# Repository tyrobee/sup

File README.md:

# Sup
A vtol that's highly customisible and reliable

i have been into the hobby of flying from planes to drone and really wanted to try and know abt the vtols from a long time and checking out there i didnt really find alot of good customisible options for vtol and in this process ive seen the zipline the company that aims to deliver stuff through drone have made their vtol for urban mobility which really inspired me and now im trying to build on my own which has the vtol capabilites for now as v1 and lets see if this goes thru well i may build that payload model as v2 ;)

The project works on a teensy 4.1 with a gyro9250 as the imu and the dRehmFlight firmware(https://github.com/nickrehm/dRehmFlight.git).

## PCB

### Front

### Back

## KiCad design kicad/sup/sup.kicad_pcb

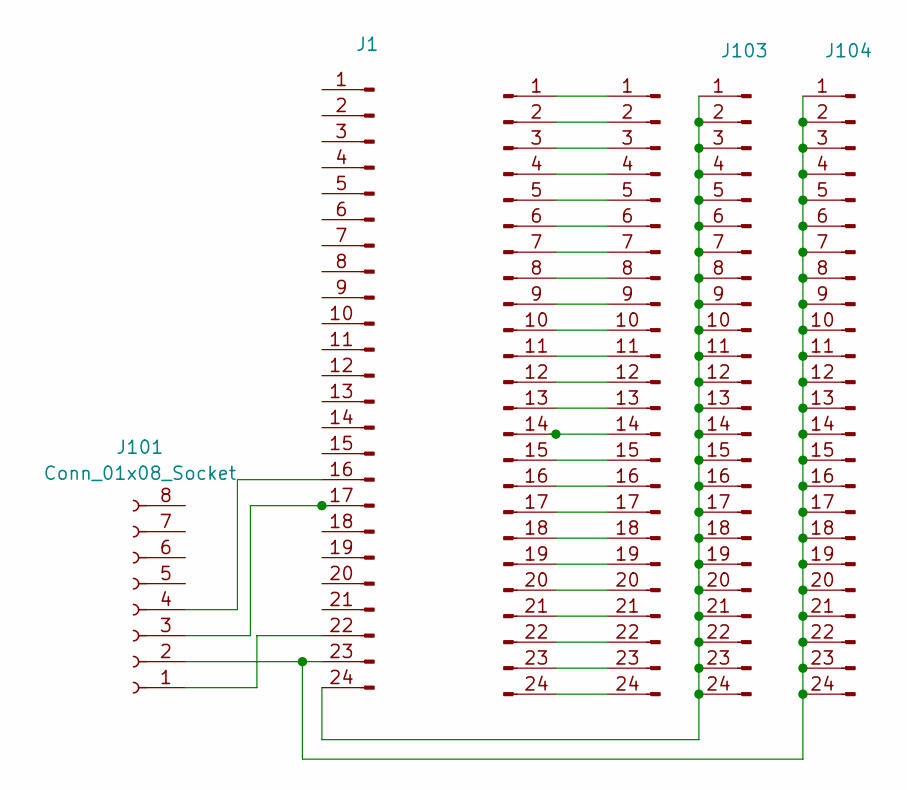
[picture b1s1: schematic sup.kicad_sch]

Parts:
J1, J2, J102, J103, J104: Conn_01x24_Pin; PinHeader_1x24_P2.54mm_Vertical
J101: Conn_01x08_Socket; PinSocket_1x08_P2.54mm_Vertical

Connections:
unnamed: J1.16, J101.4
unnamed: J1.17, J101.3
unnamed: J1.22, J101.1
unnamed: J1.23, J101.2, J104.1, J104.2, J104.3, J104.4, J104.5, J104.6, J104.7, J104.8, J104.9, J104.10, J104.11, J104.12, J104.13, J104.14, J104.15, J104.16, J104.17, J104.18, J104.19, J104.20, J104.21, J104.22, J104.23, J104.24
unnamed: J1.24, J103.1, J103.2, J103.3, J103.4, J103.5, J103.6, J103.7, J103.8, J103.9, J103.10, J103.11, J103.12, J103.13, J103.14, J103.15, J103.16, J103.17, J103.18, J103.19, J103.20, J103.21, J103.22, J103.23, J103.24
unnamed: J2.1, J102.1
unnamed: J2.2, J102.2
unnamed: J2.3, J102.3
unnamed: J2.4, J102.4
unnamed: J2.5, J102.5
unnamed: J2.6, J102.6
unnamed: J2.7, J102.7
unnamed: J2.8, J102.8
unnamed: J2.9, J102.9
unnamed: J2.10, J102.10
unnamed: J2.11, J102.11
unnamed: J2.12, J102.12
unnamed: J2.13, J102.13
unnamed: J2.14, J102.14
unnamed: J2.15, J102.15
unnamed: J2.16, J102.16
unnamed: J2.17, J102.17
unnamed: J2.18, J102.18
unnamed: J2.19, J102.19
unnamed: J2.20, J102.20
unnamed: J2.21, J102.21
unnamed: J2.22, J102.22
unnamed: J2.23, J102.23
unnamed: J2.24, J102.24

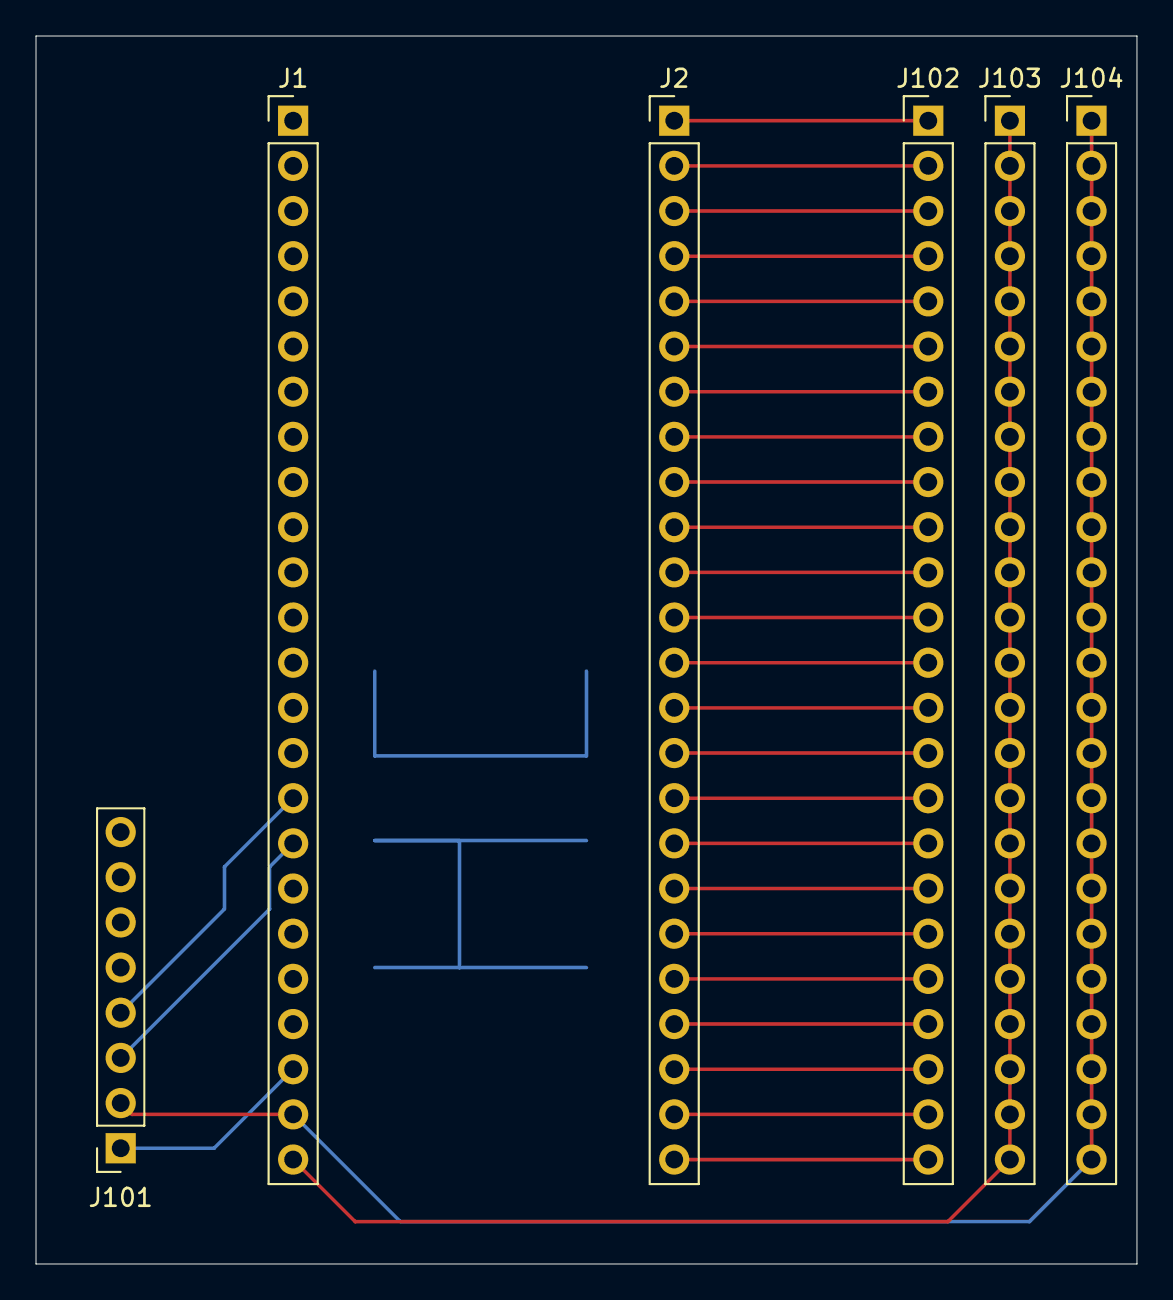
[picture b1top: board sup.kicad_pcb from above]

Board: 2 copper layers, 61.9 x 69.1 mm, 6 parts (0 on the bottom side), 29 nets.

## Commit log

2026-03-28 Fix capitalization of project name in README
    Correct capitalization of project name in README.
